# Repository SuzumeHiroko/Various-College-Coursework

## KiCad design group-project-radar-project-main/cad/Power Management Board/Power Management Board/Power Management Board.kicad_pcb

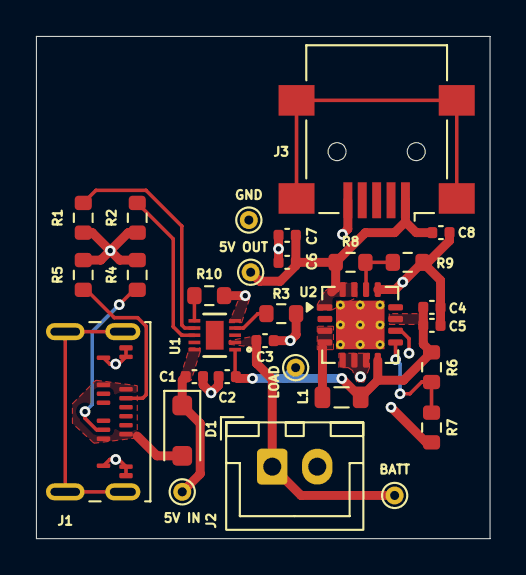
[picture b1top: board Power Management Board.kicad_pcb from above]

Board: 2 copper layers, 25.2 x 27.9 mm, 30 parts (0 on the bottom side), 15 nets.

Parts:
5V IN, 5V OUT: TestPoint; TestPoint_THTPad_D1.0mm_Drill0.5mm
BATT: TestPoint; TestPoint_THTPad_D1.0mm_Drill0.5mm
C1, C3: 1u; C_0402_1005Metric
C2, C5, C8: 10u; C_0402_1005Metric
C4: 0.1u; C_0402_1005Metric
C6: 2.2u; C_0402_1005Metric
C7: 100u; C_0402_1005Metric
D1: MBR1020VL; D_SOD-123F
GND: TestPoint; TestPoint_THTPad_D1.0mm_Drill0.5mm
J1: USB_C_Receptacle_PowerOnly_24P; USB_C_Receptacle_Amphenol_124019772112A
J2: Conn_01x02_Pin; JST_XH_B2B-XH-A_1x02_P2.50mm_Vertical
J3: USB_B_Micro; USB_Mini-B_Lumberg_2486_01_Horizontal
L1: 6.8u; L_0805_2012Metric
LOAD: TestPoint; TestPoint_THTPad_D1.0mm_Drill0.5mm
R1: 18k; R_0603_1608Metric
R2: 1k; R_0603_1608Metric
R3, R10: 10k; R_0603_1608Metric
R4, R5: 5.1k; R_0603_1608Metric
R6, R8: 1.87M; R_0603_1608Metric
R7: 340k; R_0603_1608Metric
R9: 200k; R_0603_1608Metric
U1: BQ25185DLHR; WSON10_DLH_TEX
U2: TPS61090; Texas_RSA_VQFN-16-1EP_4x4mm_P0.65mm_EP2.7x2.7mm_ThermalVias

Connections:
+5V: 5V OUT.1, C6.1, C7.1, C8.1, J3.1 (VBUS), R8.2, U2.1 (VOUT), U2.15 (VOUT), U2.16 (VOUT)
+BATT: BATT.1, C3.1, J2.1, U1.2 (BAT)
/SYS: C2.1, C4.1, C5.1, L1.1, LOAD.1, R6.2, U1.1 (SYS), U2.8 (VBAT), U2.11 (EN)
GND: C1.2, C2.2, C3.2, C4.2, C5.2, C6.2, C7.2, C8.2, GND.1, J1.A1 (GND), J1.A12 (GND), J1.B1 (GND), J1.B12 (GND), J2.2, J3.5 (GND), R1.1, R2.1, R3.1, R4.2, R5.2, R7.1, R9.1, R10.1, U1.5 (GND), U2.5 (PGND), U2.6 (PGND), U2.7 (PGND), U2.10 (SYNC), U2.13 (GND)
unnamed: D1.2 (A), J1.A4 (VBUS), J1.A9 (VBUS), J1.B4 (VBUS), J1.B9 (VBUS)
unnamed: J1.A5 (CC1), R5.1
unnamed: J1.B5 (CC2), R4.1
unnamed: L1.2, U2.3 (SW), U2.4 (SW)
unnamed: R1.2, U1.7 (ILIM/VSET)
unnamed: R2.2, U1.8 (ISET)
unnamed: R10.2, U1.6 (TS/MR)
unnamed: R3.2, U1.4 (/CE)
unnamed: R8.1, R9.2, U2.14 (FB)
unnamed: R6.1, R7.2, U2.9 (LBI)
VBUS: 5V IN.1, C1.1, D1.1 (K), U1.10 (IN)

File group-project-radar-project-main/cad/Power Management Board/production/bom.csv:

Designator,Footprint,Quantity,Value,LCSC Part #
"5V IN, 5V OUT, BATT, GND, LOAD",TestPoint_THTPad_D1.0mm_Drill0.5mm,5,TestPoint,
"C1, C3",0402,2,1u,
"C2, C5, C8",0402,3,10u,
C4,0402,1,0.1u,
C6,0402,1,2.2u,
C7,0402,1,100u,
D1,D_SOD-123F,1,MBR1020VL,
J1,USB_C_Receptacle_Amphenol_124019772112A,1,USB_C_Receptacle_PowerOnly_24P,
J2,JST_XH_B2B-XH-A_1x02_P2.50mm_Vertical,1,Conn_01x02_Pin,
J3,USB_Mini-B_Lumberg_2486_01_Horizontal,1,USB_B_Micro,
L1,0805,1,6.8u,
R1,0603,1,18k,
"R10, R3",0603,2,10k,
R2,0603,1,1k,
"R4, R5",0603,2,5.1k,
"R6, R8",0603,2,1.87M,
R7,0603,1,340k,
R9,0603,1,200k,
U1,WSON10_DLH_TEX,1,BQ25185DLHR,
U2,Texas_RSA_VQFN-16-1EP_4x4mm_P0.65mm_EP2.7x2.7mm_ThermalVias,1,TPS61090,
